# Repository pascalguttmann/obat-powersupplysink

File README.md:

# Obat - PowerSupplySink

KiCAD Project for the PowerSupplySink.

| TOP | BOT |
| ------------- | -------------- |
|   |  |
|  |  |
|  |  |

## License

This repository is licensed under the MIT license.

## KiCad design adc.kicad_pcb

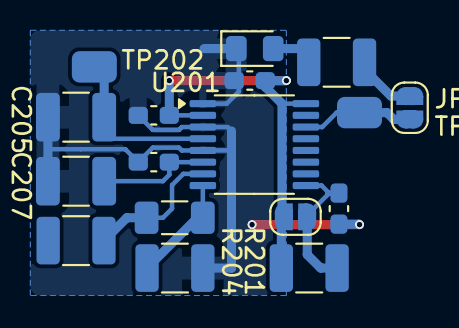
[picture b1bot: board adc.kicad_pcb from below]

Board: 2 copper layers, 17 parts (17 on the bottom side), 10 nets.

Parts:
C201, C202, C203, C206: 1u; C_0603_1608Metric_Pad1.08x0.95mm_HandSolder
C204: 47n; C_1206_3216Metric_Pad1.33x1.80mm_HandSolder
C205, C207: 10u; C_1210_3225Metric_Pad1.33x2.70mm_HandSolder
D201: LED; LED_0805_2012Metric_Pad1.15x1.40mm_HandSolder
JP201: SolderJumper_2_Open; SolderJumper-2_P1.3mm_Open_RoundedPad1.0x1.5mm
JP202: SolderJumper_2_Bridged; SolderJumper-2_P1.3mm_Bridged-Soldermask-Paste_RoundedPad1.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
R201: 1k; R_1210_3225Metric_Pad1.30x2.65mm_HandSolder
R202: 10k; R_1210_3225Metric_Pad1.30x2.65mm_HandSolder
R203, R204: 100; R_1210_3225Metric_Pad1.30x2.65mm_HandSolder
TP201, TP202: TP_0805_2012Metric
U201: ADS8665IPWR; TSSOP-16_4.4x5mm_P0.65mm

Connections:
+5VA_adc: C202.2, C203.2, JP201.1 (A), R201.1, U201.2 (AVDD), U201.16 (DVDD)
/AIN_GND: C204.1, R204.1, U201.8 (AIN_GND)
/AIN_P_int: C204.2, R203.1, U201.7 (AIN_P)
/GPO: JP202.2 (B), TP201.1, U201.14 (ALARM/SDO-1/GPO)
/GPO_JMP: JP202.1 (A), R202.1
/GPO_LED: D201.2 (A), R202.2
/REFCAP: C206.2, C207.2, U201.6 (REFCAP)
/REFIO: C205.2, TP202.1, U201.4 (REFIO)
/~RST: C201.2, JP201.2 (B), R201.2, U201.9 (~RST)
GND: C201.1, C202.1, C203.1, C205.1, C206.1, C207.1, D201.1 (K), R204.2, U201.1 (DGND), U201.3 (AGND), U201.5 (REFGND)

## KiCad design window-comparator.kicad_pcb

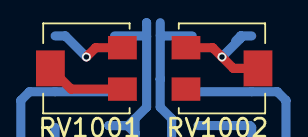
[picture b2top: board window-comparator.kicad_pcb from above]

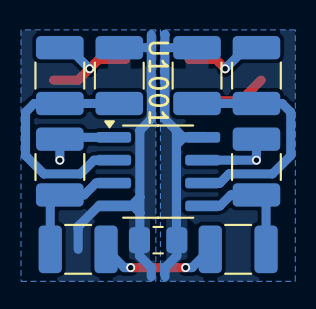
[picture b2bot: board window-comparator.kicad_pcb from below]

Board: 2 copper layers, 12 parts (10 on the bottom side), 12 nets.

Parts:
C1001: 100n; C_0805_2012Metric_Pad1.18x1.45mm_HandSolder
R1001, R1004: 100k; R_1210_3225Metric_Pad1.30x2.65mm_HandSolder
R1002, R1003: 22; R_1210_3225Metric_Pad1.30x2.65mm_HandSolder
R1005, R1006: 0; R_1210_3225Metric_Pad1.30x2.65mm_HandSolder
R1007, R1008: 1M; R_1210_3225Metric_Pad1.30x2.65mm_HandSolder
RV1001, RV1002: 1k; Potentiometer_Bourns_PVG5H
U1001: TLV9352; SOIC-8_3.9x4.9mm_P1.27mm

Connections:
+10V_compare-logic: C1001.2, R1001.1, U1001.8 (V+)
-5V_compare-logic: C1001.1, R1004.2, U1001.4 (V-)
/l+: R1006.2, R1008.1, U1001.3 (+)
/l-: R1003.2, R1004.1, U1001.2 (-)
/lpot: R1003.1, RV1002.2, RV1002.3
/meas: R1005.1, R1006.1
/u+: R1005.2, R1007.1, U1001.5 (+)
/u-: R1001.2, R1002.1, U1001.6 (-)
/ul: RV1001.2, RV1001.3
/ule: R1007.2, U1001.7
/upot: R1002.2, RV1001.1
/~lle: R1008.2, U1001.1

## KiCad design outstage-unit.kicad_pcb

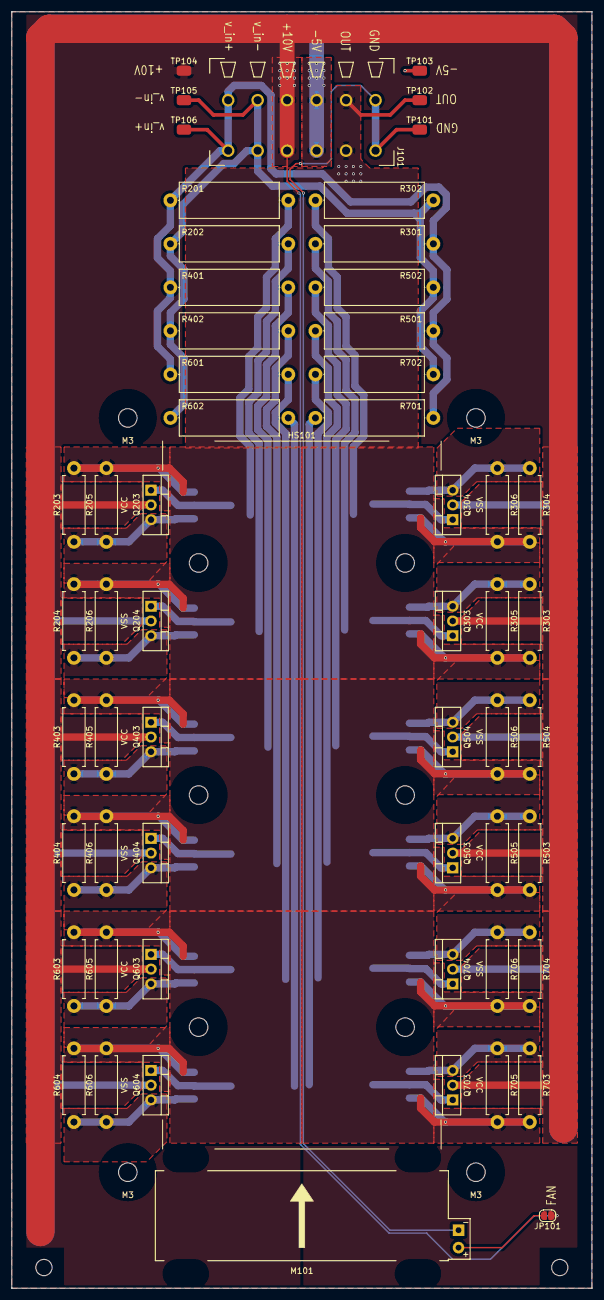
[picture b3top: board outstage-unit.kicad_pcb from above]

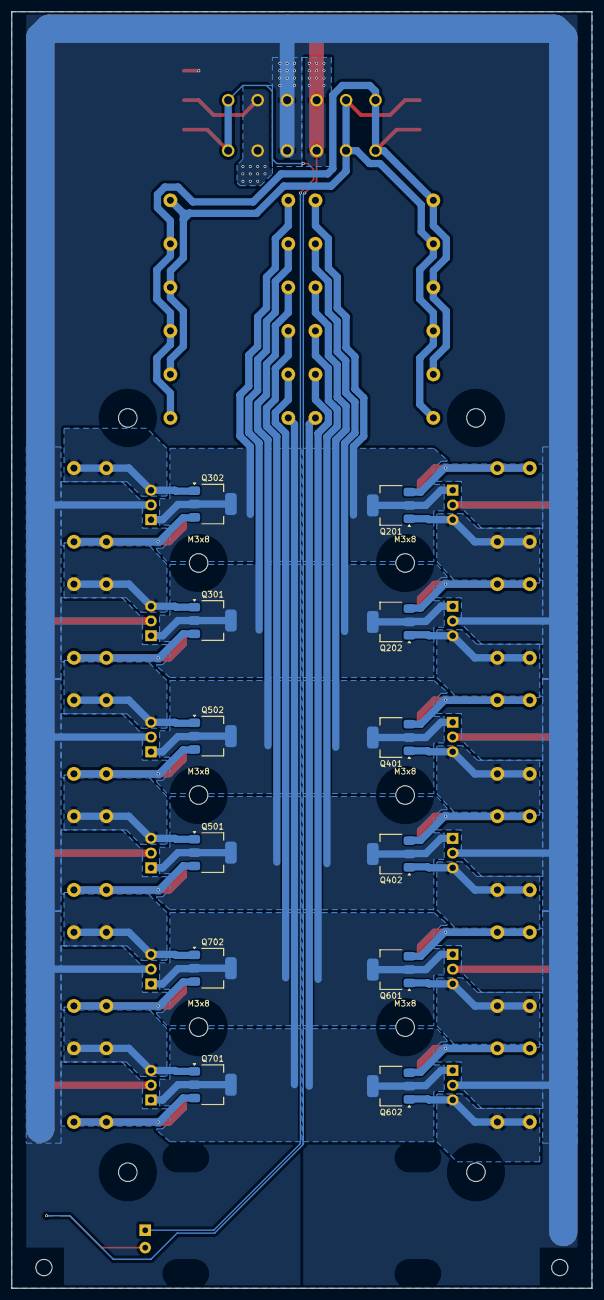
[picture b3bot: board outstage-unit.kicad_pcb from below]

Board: 2 copper layers, 100.0 x 220.0 mm, 70 parts (12 on the bottom side), 31 nets.

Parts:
HS101: SK499-120 SA; Heatsink_Fischer_SK499-120_46x120mm_h33mm_Drill3.5mm_ScrewM3
J101: Conn_01x06_Socket; PhoenixContact_TDPT_2,5_6-SP-5,08_1x06_P5.08mm_Horizontal
JP101: SolderJumper_2_Bridged; SolderJumper-2_P1.3mm_Bridged-Soldermask-Paste_RoundedPad1.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
M101: Fan; Fan_SameSky_CFM-5015V
Q201, Q301, Q401, Q501, Q601, Q701: DNLS350E; SOT-223-3_TabPin2
Q202, Q302, Q402, Q502, Q602, Q702: DPLS350E; SOT-223-3_TabPin2
Q203, Q303, Q403, Q503, Q603, Q703: TIP41C; TO-220-3_Vertical
Q204, Q304, Q404, Q504, Q604, Q704: TIP42C; TO-220-3_Vertical
R201, R202, R301, R302, R401, R402, R501, R502, R601, R602, R701, R702: 22; R_Axial_DIN0617_L17.0mm_D6.0mm_P20.32mm_Horizontal
R203, R204, R205, R206, R303, R304, R305, R306, R403, R404, R405, R406, R503, R504, R505, R506, R603, R604, R605, R606, R703, R704, R705, R706: 680m; R_Axial_DIN0411_L9.9mm_D3.6mm_P12.70mm_Horizontal
TP101, TP102, TP103, TP104, TP105, TP106: TP_0805_2012Metric

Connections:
/+10V: J101.4, JP101.1 (A), Q203.2 (C), Q303.2 (C), Q403.2 (C), Q503.2 (C), Q603.2 (C), Q703.2 (C), TP104.1
/-5V: J101.3, Q204.2 (C), Q304.2 (C), Q404.2 (C), Q504.2 (C), Q604.2 (C), Q704.2 (C), TP103.1
/GND: J101.1, M101.2 (-), TP101.1
/v_in+: J101.6, R201.1, R301.1, R401.1, R501.1, R601.1, R701.1, TP106.1
/v_in-: J101.5, R202.1, R302.1, R402.1, R502.1, R602.1, R702.1, TP105.1
/v_out: J101.2, Q201.3 (E), Q202.3 (E), Q301.3 (E), Q302.3 (E), Q401.3 (E), Q402.3 (E), Q501.3 (E), Q502.3 (E), Q601.3 (E), Q602.3 (E), Q701.3 (E), Q702.3 (E), R203.2, R204.1, R205.2, R206.1, R303.2, R304.1, R305.2, R306.1, R403.2, R404.1, R405.2, R406.1, R503.2, R504.1, R505.2, R506.1, R603.2, R604.1, R605.2, R606.1, R703.2, R704.1, R705.2, R706.1, TP102.1
unnamed: JP101.2 (B), M101.1 (+)
unnamed: Q201.1 (B), Q203.3 (E), R203.1, R205.1
unnamed: Q201.2 (C), Q203.1 (B), R201.2
unnamed: Q202.1 (B), Q204.3 (E), R204.2, R206.2
unnamed: Q202.2 (C), Q204.1 (B), R202.2
unnamed: Q301.1 (B), Q303.3 (E), R303.1, R305.1
unnamed: Q301.2 (C), Q303.1 (B), R301.2
unnamed: Q302.1 (B), Q304.3 (E), R304.2, R306.2
unnamed: Q302.2 (C), Q304.1 (B), R302.2
unnamed: Q401.1 (B), Q403.3 (E), R403.1, R405.1
unnamed: Q401.2 (C), Q403.1 (B), R401.2
unnamed: Q402.1 (B), Q404.3 (E), R404.2, R406.2
unnamed: Q402.2 (C), Q404.1 (B), R402.2
unnamed: Q501.1 (B), Q503.3 (E), R503.1, R505.1
unnamed: Q501.2 (C), Q503.1 (B), R501.2
unnamed: Q502.1 (B), Q504.3 (E), R504.2, R506.2
unnamed: Q502.2 (C), Q504.1 (B), R502.2
unnamed: Q601.1 (B), Q603.3 (E), R603.1, R605.1
unnamed: Q601.2 (C), Q603.1 (B), R601.2
unnamed: Q602.1 (B), Q604.3 (E), R604.2, R606.2
unnamed: Q602.2 (C), Q604.1 (B), R602.2
unnamed: Q701.1 (B), Q703.3 (E), R703.1, R705.1
unnamed: Q701.2 (C), Q703.1 (B), R701.2
unnamed: Q702.1 (B), Q704.3 (E), R704.2, R706.2
unnamed: Q702.2 (C), Q704.1 (B), R702.2

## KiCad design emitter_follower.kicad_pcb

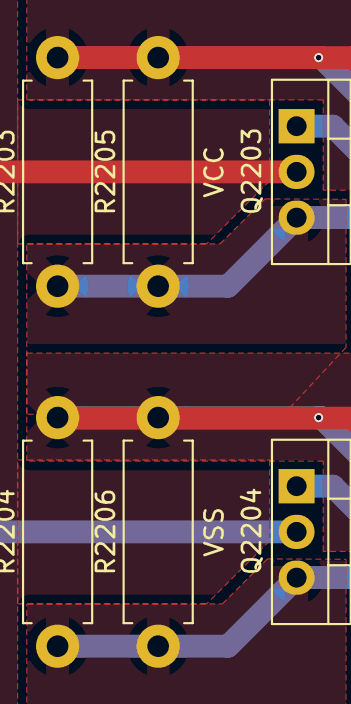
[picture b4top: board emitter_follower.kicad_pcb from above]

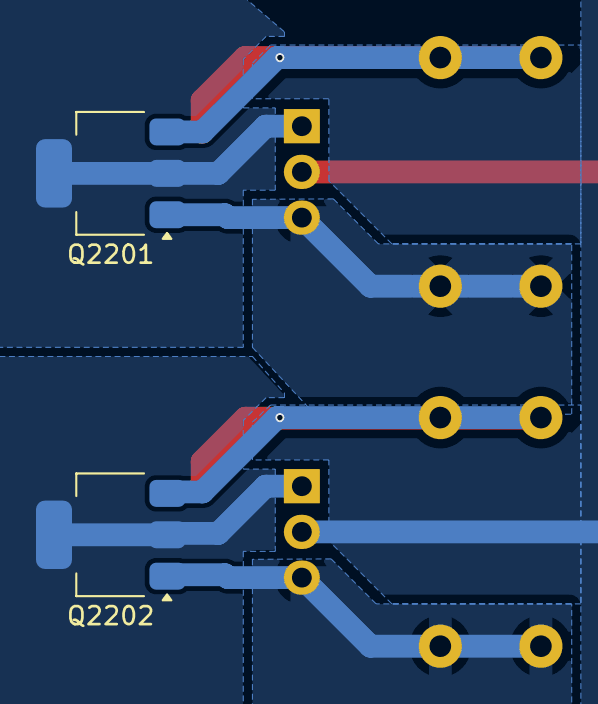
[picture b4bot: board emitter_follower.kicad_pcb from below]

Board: 2 copper layers, 8 parts (2 on the bottom side), 5 nets.

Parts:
Q2201: DNLS350E; SOT-223-3_TabPin2
Q2202: DPLS350E; SOT-223-3_TabPin2
Q2203: TIP41C; TO-220-3_Vertical
Q2204: TIP42C; TO-220-3_Vertical
R2203, R2204, R2205, R2206: 680m; R_Axial_DIN0411_L9.9mm_D3.6mm_P12.70mm_Horizontal

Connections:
/1: Q2201.1 (B), Q2203.3 (E), R2203.1, R2205.1
/2: Q2202.1 (B), Q2204.3 (E), R2204.2, R2206.2
/3: Q2201.2 (C), Q2203.1 (B)
/4: Q2202.2 (C), Q2204.1 (B)
/v_out: Q2201.3 (E), Q2202.3 (E), R2203.2, R2204.1, R2205.2, R2206.1

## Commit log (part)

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2024-05-21 add KiCad gitignore
2024-05-21 add pss project
2024-05-21 ignore ~ files
2024-05-21 deduplicate root directory
2024-05-21 add schematic page settings
2024-05-21 increase ERC strictness
2024-05-21 gitingore autosaved file
2024-05-21 change annotation rule to x1000
2024-05-21 add hierarchical outstage sheet
2024-05-22 add outstage with emitter follower
2024-05-22 add bias stage, add empty MPN property
2024-05-22 schematic version bump 0.1.0
2024-05-22 export schematic 0.1.0
2024-05-23 add readme and license
2024-05-23 ignore vim swap files
2024-05-23 enhance readme
2024-05-26 change rubber diode vbe multiplier trimmer position
    changed position prohibits excess dropoff voltage in case of machanical failure of trimmer
2024-05-26 fix wrong part number of current limiting transistors in outstage
2024-06-02 add heatsinks, thermal pads, mounting clips
2024-06-02 add fans for heatsink thermal management
2024-06-02 bump schematic version to 0.3.0
2024-09-27 add control opamp and VPN field
2024-09-27 add control subtraction junction
2024-09-27 add control pid circuit
2024-09-27 add control opamp power decoupling
2024-09-27 fix ERC error: unconnected pins
2024-10-05 add limit-logic SR Latch CD4044
2024-10-05 add limit-logic state nets at latch output
2024-10-08 move symbols to project specific library
2024-10-08 add limit-logic mode NOR gate 4078
2024-10-08 add limit-logic pull ups/downs for input pins
2024-10-08 fix limit-logic SR latch positiv logic 4043
    4043 is positive logic, not wrongly used 4044
2024-10-08 fix limit-logic 4043 symbol
2024-10-08 add limit-logic 4081 2 input nand gate
2024-10-08 add limit-logic 4073 3 input nand gate
2024-10-08 add limit-logic 4071 2 input or gate
2024-10-11 add limit-logic 4069 hex inverter
2024-10-11 refactor schematic hirarchy
2024-10-11 add limit-logic mode transition logic
2024-10-11 add limit-logic pull ups for tristate of mode latches
2024-10-11 add limit-logic compare-logic hierachical sheet and hirarchy connectors
2024-10-18 add limit-logic comparator opamp tlv9352
2024-10-23 add compare-logic windows comparator
2024-10-23 add window-comparator hirarchical sheet
2024-10-23 add compare-logic decoupling capacitor
2024-10-25 fix window-comparator accept two limit inputs
2024-10-25 add window-comparator multiple instances for all configured limits and refs
2024-10-25 add compare-logic conf_refselect hirarchical input
2024-10-25 add compare-logic 4019 select gate
2024-10-25 add compare-logic input pull up for unused inverters
2024-10-25 fix missing footprints, MPN, VPN and datasheet info in BOM
2024-10-28 add limit-logic hierarchical labels
2024-10-28 add power-electronics hierarchical label
2024-10-28 bump schematic version to 0.5.0
2024-11-06 change window-comparator quiescent current of schmitt-trigger
    increase the quiescent current of the schmitt trigger by a factor of 10 to avoid usage of 10MOhm resistor
    this will yield a minimum quiescent current of 5µA > 10pA (comparator input bias current)
2024-11-06 bump schematic version to 0.5.1
2024-11-07 fix limit-logic mode pull downs
    limit-logic should implement gapping switching between modes to avoid short circuit of active sources
    connected during the transition. The same behavior should be implemented in case of the tri-state output
    of the rs-latch is used. Hence, a pull down (NOT a pull up) is required for the modes.
2024-11-07 bump schematic version to 0.5.2
2024-11-07 fix mode-transition to allow transition between limitmodes
2024-11-07 edit limit-logic logic gate assignment
2024-11-07 add mode-transition missing part number and footprint
2024-11-07 bump schematic version to 0.5.3
2024-11-08 add mux hierarchical sheet
2024-11-08 add mux 4066 quad bilateral switch
2024-11-11 add mux schematic
2024-11-12 bump schatic version to 0.6.0
2024-11-13 fix control difference junction switched inputs
2024-11-13 fix control pid controller circuit
    circuit in Europalehrbuch Tabellenbuch Elektrotechnik which is listed under 'pid controller' is not a pid controller.
    circuit is redesigned as described in docs by designing the pid with RC networks.
2024-11-13 add control pid anit integral windup diodes
2024-11-13 bump schematic version to 0.6.1
2024-11-14 edit control pid parameters to be ready for 1MHz pole of current sensor
2024-11-14 bump schematic version to 0.6.2
2024-11-14 edit control enhance component reuse
2024-11-14 bump schematic version to 0.6.3
2024-11-15 add measurement hierarchical sub circuit
2024-11-15 add measurement hierarchical labels
2024-11-15 bump schematic version to 0.7.0
2024-11-18 fix control sign of reference and measured signal
2024-11-19 add relay sub circuit
2024-11-19 bump schematic version to 0.8.0
2024-11-19 edit window-comparator feedback prof spiegelberg, remove hysteresis at window comparator
2024-11-19 edit window-comparator feedback prof spiegelberg, add trimmer to window generation
2024-11-19 edit bias and measurement to reuse smd trimmer instead of tht trimmer
2024-11-20 edit control feedback from prof spiegelberg, adjust input offset correction resistor
2024-11-21 edit control feedback from prof spiegelberg, make pid control parameters independently adjustable
2024-11-21 edit control setting point for KP = 10 at trimmer changed
    changed the fixed resistance, so that the setting for KP = 10 is at 50% turn.
2024-11-25 edit control set pid parameters as per controller design of bandwidth limited controller
2024-11-25 edit trimmers use adjustmentstyle 'top' for trimmers
2024-11-25 bump schematic version to 0.8.1
2024-11-25 fix control missing bandwidth limitation of proportional term
2024-11-26 add conf DAC AD5672R symbol to library
2024-11-27 add conf hierarchical spi input
2024-11-27 add conf checker logic
2024-11-27 add conf analog comparator for limits
2024-11-27 add conf hierarchical pins
2024-11-27 edit relay invert input logic
2024-11-27 add adc hierarchical sub circuit
2024-11-28 add digital-interface component
2024-11-28 edit pss remove stray power symbol
2024-11-28 fix adc lowpass filter frequency
2024-11-29 bump schematic version to 0.9.0
2024-11-29 add conf SCKL inverter
2024-11-29 bump schematic version to 0.9.1
2024-11-30 add power sub circuit
2024-12-02 add power power checker
2024-12-02 bump schematic to version 0.10.1
2024-12-02 add leds as visual indicators for internal state
2024-12-02 bump schematic version to 0.11.0
2024-12-03 add esd tvs diodes and fuses
2024-12-03 bump schematic version to 0.12.0
2024-12-03 add pss connectors for interfacing with external components
2024-12-03 edit pss individual power nets for sub circuits
2024-12-03 pss fix ERC errors bus and hierarchical connection
2024-12-03 fix digital-interface ERC error wrong connection of ESD diode pins
2024-12-03 fix pss ERC error unconnected labels
2024-12-03 fix pss ERC error: missing power flag
2024-12-03 fix pss ERC errors: multiple outputs connected
2024-12-03 fix outstage ERC error: fans connected to 24V not 10V
2024-12-03 bump schematic version to 0.12.1
2024-12-04 add pss 3dmodels and testpoints
2024-12-04 fix pss missing not connected pins in symbols
2024-12-04 add outstage separation by connectors for individual PCB
2024-12-04 add bias separate power supply net
2024-12-04 edit pss alphabetically order pages
2024-12-04 edit pss reannotate entire schematic
2024-12-04 edit pss symbol library: export all schematic symbols to library 'pss' and update symbol link
2024-12-04 edit pss footprint library: export all footprints to library 'pss' and update footprint links
2024-12-04 bump schematic version to 0.13.0
2024-12-04 add pss datasheets offline
2024-12-04 bump schematic version to 0.13.1
2024-12-04 fix readme lineendings and markdown heading style
2024-12-05 add control solder jumper to deactivate anti-integral windup
2024-12-05 bump schematic version to 0.13.2
2024-12-07 add pss netclass definition
2024-12-07 bump schematic version to 0.13.3
2024-12-07 edit pss pcb update to sch-0.13.3
2024-12-07 add pcb default grid settings
2024-12-07 edit pcb page layout settings
2024-12-07 edit pcb soldermask expansion
2024-12-07 add pcb design rules
2024-12-07 fix soldermask expansion DRC error for bridging
2024-12-07 add pcb predefined track sizes for finer width selection depending on current
2024-12-07 add pcb edge clearance keepout area
2024-12-07 add pcb mounting holes for stacking via M3x60 hexnuts
2024-12-07 edit trimmer adjustment style to sideways
2024-12-08 add pcb sub layout for emitter-follower
2024-12-08 add pcb outstage-unit sub circuit layout of power-electronics
2024-12-08 edit outstage connector pin out for outstage-unit
    enhance layout option with other pin out and mirror pinout for second outstage.
    This allows to create a better layout with less crossing of high current tracks.
2024-12-08 add pcb sub circuit outstage-unit
2024-12-08 edit heatsink mounting holes position, fix copper pour
2024-12-08 fix pcb outstage-unit DRC errors
2024-12-08 add pcb outstage-unit silkscreen notes
2024-12-08 add pcb outstage-unit as sub layout
2024-12-08 bump board version to 0.1.0
2024-12-08 fix layout emitter_follower plane overhang prohibits zonefill
2024-12-08 bump board version to 0.1.1
2024-12-08 fix schematic netlist error, two nets with same name
2024-12-08 add pcb connector copper planes
2024-12-08 remove pss solder jumper in output current flow around measurement sub circuit
2024-12-09 add pcb outstage-connector copper planes
2024-12-09 edit pcb connector, switch placement for via free routing of power
2024-12-09 fix pcb outstage-unit zone priority
2024-12-09 add pcb power trace from connectors to outstage-unit connectors
2024-12-09 add pcb power supply rails as zones for whole pcb
2024-12-09 bump board version to 0.2.0
2024-12-09 add pcb layout of relay sub circuit
2024-12-09 add pcb layout of measurement sub circuit
2024-12-09 remove measurement duplicate testpoint
2024-12-09 add pcb layout for esd protection diodes
2024-12-09 remove power redundant esd protection diode
2024-12-09 fix outstage-unit symbol of heatsink, the heatsink is isolated
2024-12-09 add pss lightpipe to schematic
2024-12-10 fix pss lightpipe length variant selection
2024-12-10 add pcb layout for led indicator placement
2024-12-10 fix bias heatsink unconnected electrical connection
2024-12-10 add pcb layout for bias stage
2024-12-10 bump board version to 0.5.0
2024-12-10 edit digital-interface use bipolar esd diodes for layout
2024-12-10 add pcb layout for digital-interface sub-circuit
2024-12-10 add pcb layout for adc sub circuit as hierarchical layout
2024-12-10 add pcb layout for adc sub circuit
2024-12-11 add pcb layout for mux sub circuit
2024-12-11 edit mux remove duplicate test points
2024-12-11 add pcb layout for connection of adc circuit
2024-12-12 add pcb layout for conf sub circuit - prototype
2024-12-12 add pcb layout for conf sub circuit
2024-12-12 add pcb layout for compare-logic sub circuit - prototype
2024-12-13 add pcb layout for window-comparator sub circuit
2024-12-13 add pcb layout for compare-logic sub circuit
2024-12-13 add pcb layout for subcircuit limit-logic
2024-12-13 edit pcb layout for limit-logic decrease trace width
2024-12-13 add pcb layout for mode-transition sub circuit - internal connection
2024-12-14 add pcb layout for mode-transition sub circuit
2024-12-14 fix pcb layout DRC errors
2024-12-14 add pcb layout for silkscreen layers
2024-12-14 add pcb version marking and logo
2024-12-14 add kikit separate batch file for windows
2024-12-14 add gerber export
2024-12-14 edit 3d model of heatsink
2024-12-15 add readme images of 3d model
2025-01-20 add interactive html bom
